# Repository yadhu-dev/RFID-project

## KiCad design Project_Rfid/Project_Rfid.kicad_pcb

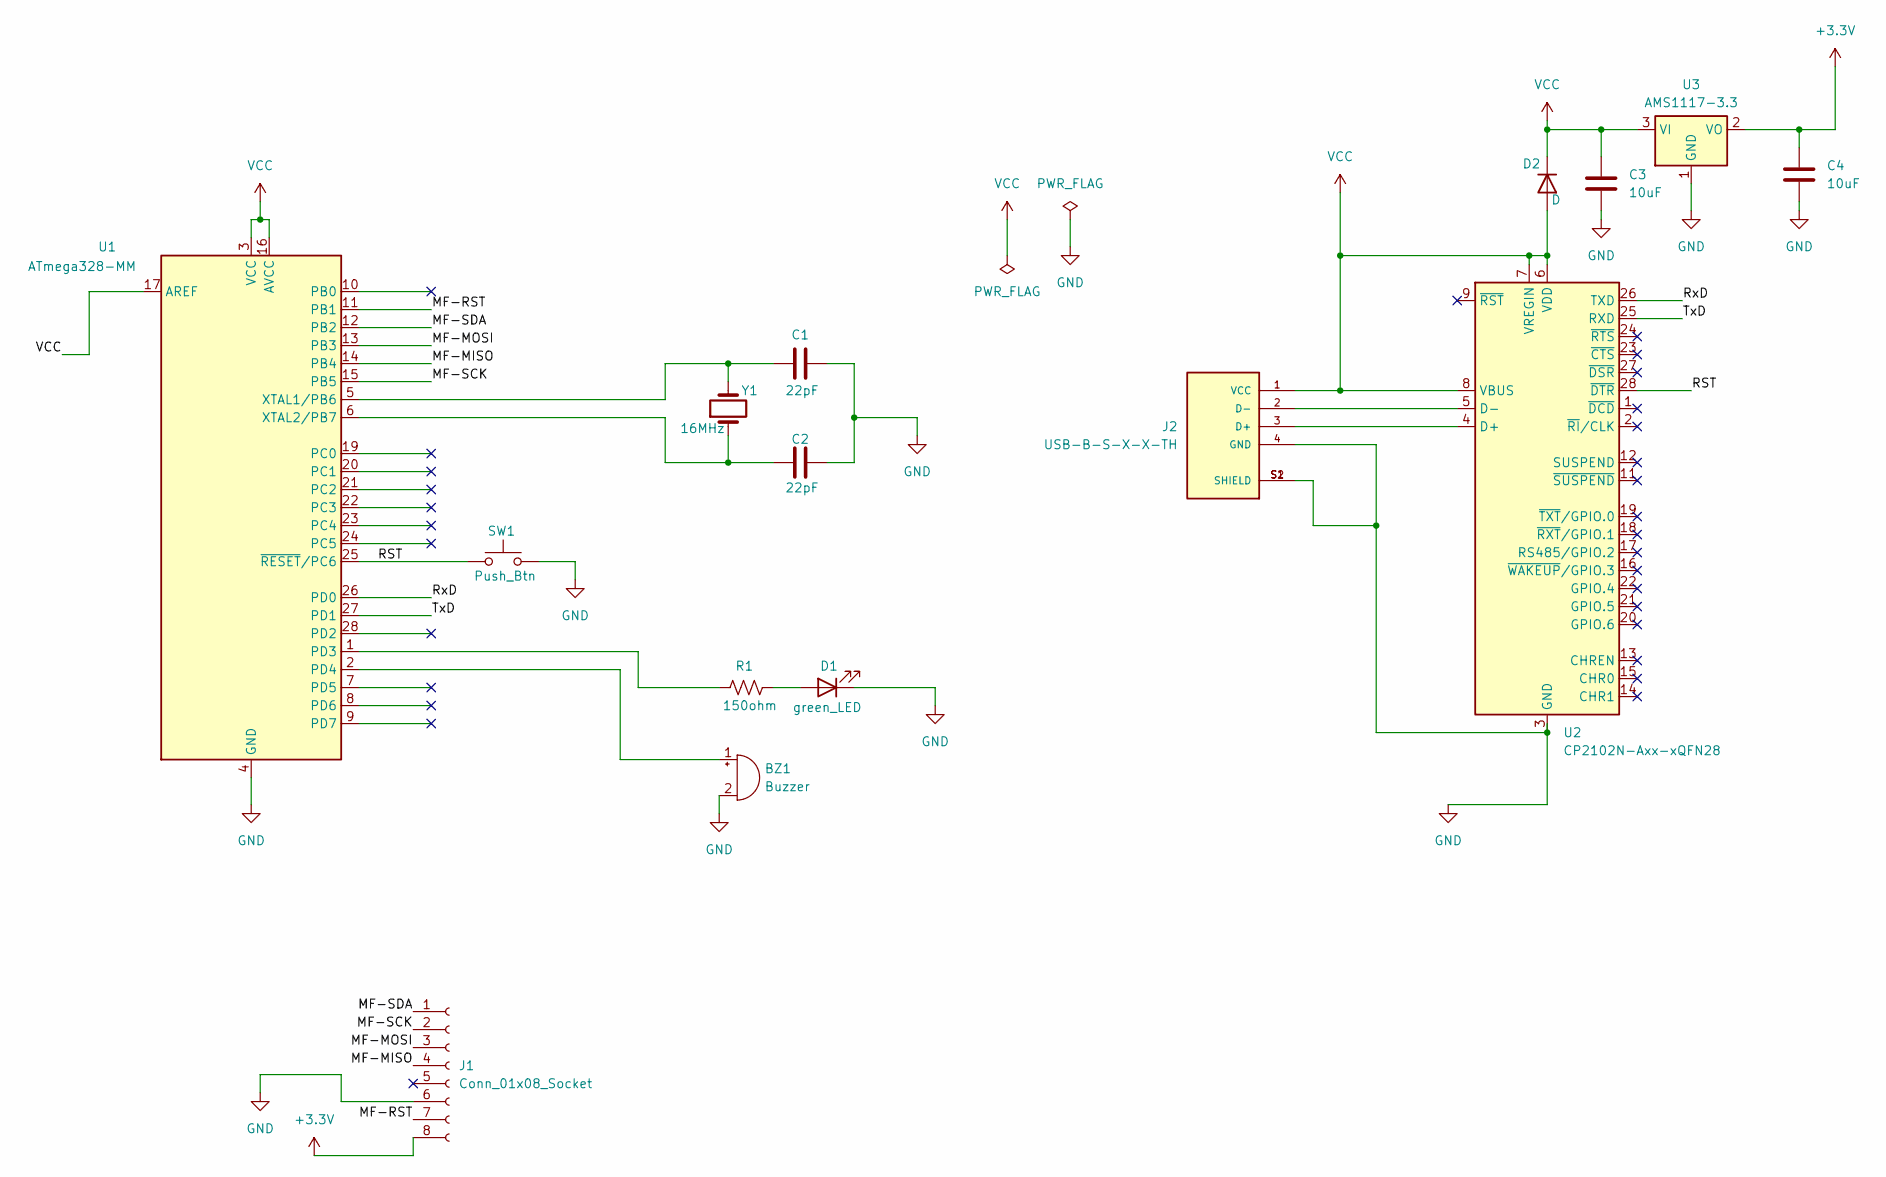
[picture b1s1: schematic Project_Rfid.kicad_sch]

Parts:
BZ1: Buzzer; Buzzer_TDK_PS1240P02BT_D12.2mm_H6.5mm
C1, C2: 22pF; C_0603_1608Metric
C3, C4: 10uF; C_0603_1608Metric
D1: green_LED; LED_1812_4532Metric
D2: D; D_0603_1608Metric
J1: Conn_01x08_Socket; PinHeader_1x08_P2.54mm_Vertical
J2: USB-B-S-X-X-TH; USB_B_Type_dwned; PARTREV Q
R1: 150ohm; R_0603_1608Metric
SW1: Push_Btn; SW_PUSH_6mm_H5mm
U1: ATmega328-MM; QFN-28-1EP_4x4mm_P0.45mm_EP2.4x2.4mm
U2: CP2102N-Axx-xQFN28; QFN-28-1EP_5x5mm_P0.5mm_EP3.35x3.35mm
U3: AMS1117-3.3; SOT-223-3_TabPin2
Y1: 16MHz; Crystal_HC49-4H_Vertical

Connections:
+3.3V: C4.1, J1.8, U3.2 (VO)
/MF-MISO: J1.4, U1.14 (PB4)
/MF-MOSI: J1.3, U1.13 (PB3)
/MF-RST: J1.7, U1.11 (PB1)
/MF-SCK: J1.2, U1.15 (PB5)
/MF-SDA: J1.1, U1.12 (PB2)
/RST: SW1.1, U1.25 (~RESET/PC6), U2.28 (~DTR)
/RxD: U1.26 (PD0), U2.26 (TXD)
/TxD: U1.27 (PD1), U2.25 (RXD)
GND: BZ1.2 (-), C1.2, C2.2, C3.2, C4.2, D1.1 (K), J1.6, J2.4 (GND), J2.S1 (SHIELD), J2.S2 (SHIELD), SW1.2, U1.4 (GND), U1.18 (GND), U1.29 (GND), U2.3 (GND), U2.29 (GND), U3.1 (GND)
unnamed: BZ1.1 (+), U1.2 (PD4)
unnamed: D1.2 (A), R1.2
unnamed: J2.3 (D+), U2.4 (D+)
unnamed: J2.2 (D-), U2.5 (D-)
unnamed: R1.1, U1.1 (PD3)
unnamed: C1.1, U1.5 (XTAL1/PB6), Y1.2
unnamed: C2.1, U1.6 (XTAL2/PB7), Y1.1
VCC: C3.1, D2.1 (K), D2.2 (A), J2.1 (VCC), U1.3 (VCC), U1.16 (AVCC), U1.17 (AREF), U2.6 (VDD), U2.7 (VREGIN), U2.8 (VBUS), U3.3 (VI)

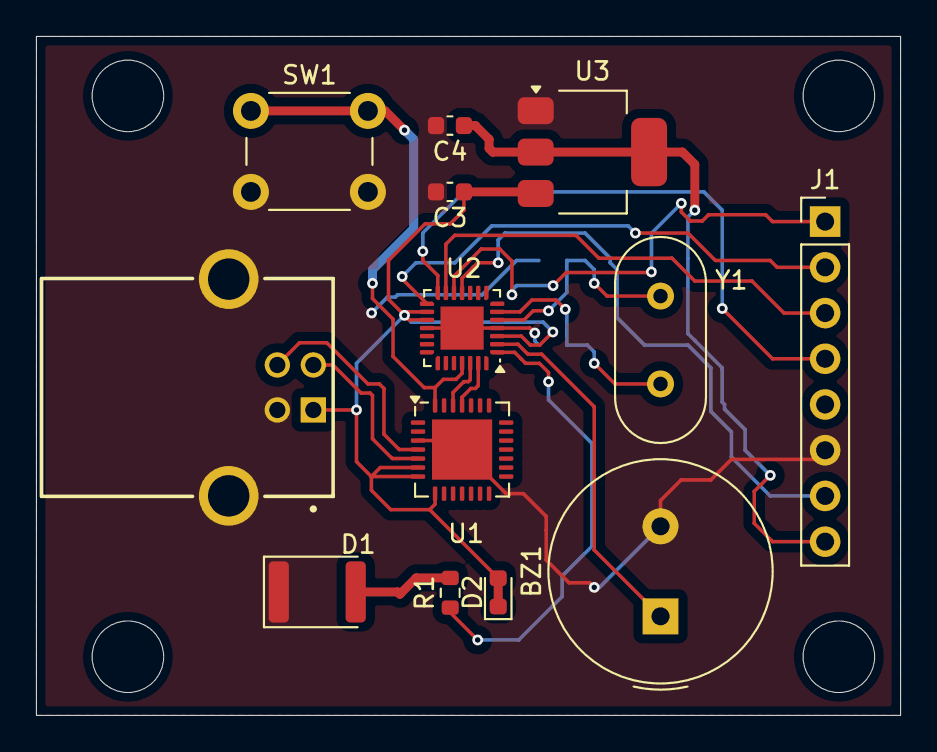
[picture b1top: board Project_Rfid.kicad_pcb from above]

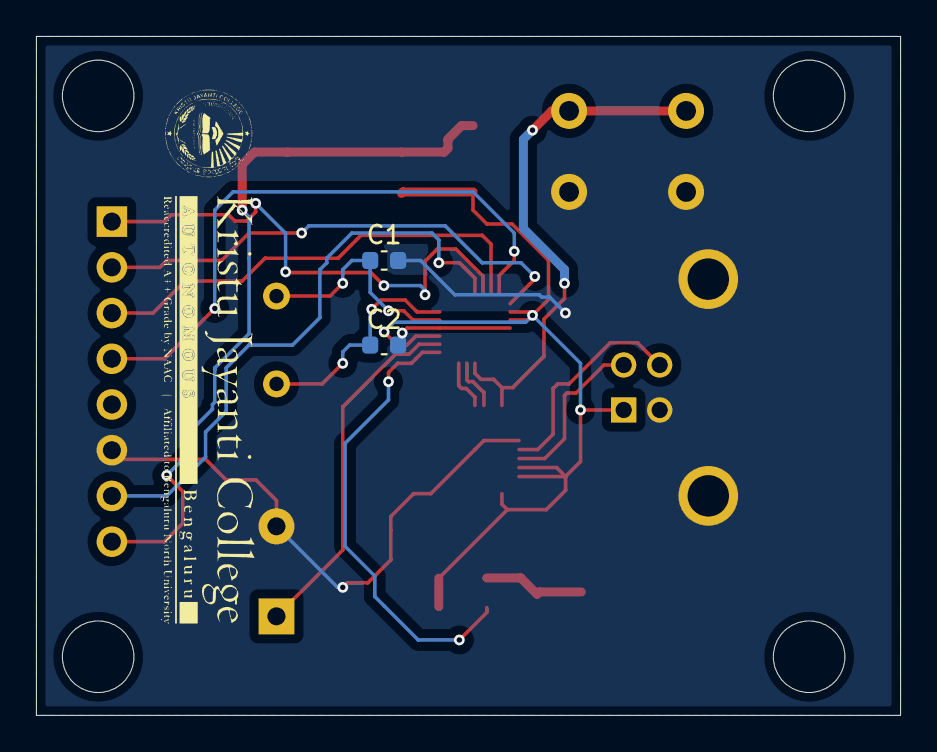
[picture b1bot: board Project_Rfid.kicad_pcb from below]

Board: 2 copper layers, 48.0 x 37.7 mm, 15 parts (2 on the bottom side), 18 nets.

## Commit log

2024-07-10 AntiTheft.cpp
2024-07-10 BookIussue.py
2024-07-10 Book_id.py
2024-07-10 BookIssue.py
2024-07-10 Assign.html
2024-07-10 Issue.html
2024-07-10 login.html
2024-07-10 Assign.css
2024-07-10 KiCad_files
2024-07-10 index.html
2024-07-10 write.html
2024-07-21 Attendance in Excel sheet
2024-07-21 Python Flask code
2024-07-21 html files
2024-07-21 Arduino Code
2024-08-10 PN5180-ReadAllBlocks.ino
    This Program is to Read all the Blocks in ISO15693 RFID Tags
2024-08-10 PN5180-ReadSpecificBlock.ino
2024-08-10 Used to Write Data in 3rd Block
2024-08-10 To Read Written Data in 3rd block
2024-08-10 To Write Data in 3rd Block
2024-08-16 Installtion files
2024-08-16 ID-Scanner batch files
2024-08-16 icon
